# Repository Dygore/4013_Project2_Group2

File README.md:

# ECEN 4013 Project 2 Group 2

## About
This project is for Group 2's ECEN 4013 project 2, all of the code contained will be documented and cited if needed. The goal of this project is to create a circuit that can transmit IMU and GPS data through 3 means of communication (USB, UHF RF, and SD Card). This Github project will be used to store all of the code architecture, the details of the project are still being finalized and will be updated soon!

## Details
The current plan is to have two seperate circuits based on difficulty. The first circuit will be the main focus with the details contained below, the second circuit details have not been finalized yet.

Micro controller: Raspberry Pi Pico  
GPS: Adafruit Mini GPS PA1010D  
Radio: HC05  
IMU: Adafruit BNO055  
SD Card:  HW-125 SPI Micro SD Board  
Battery: LP103454  

## References
-https://microcontrollerslab.com/neo-6m-gps-module-raspberry-pi-pico-micropython/

Dylan Gore 10/24/2022

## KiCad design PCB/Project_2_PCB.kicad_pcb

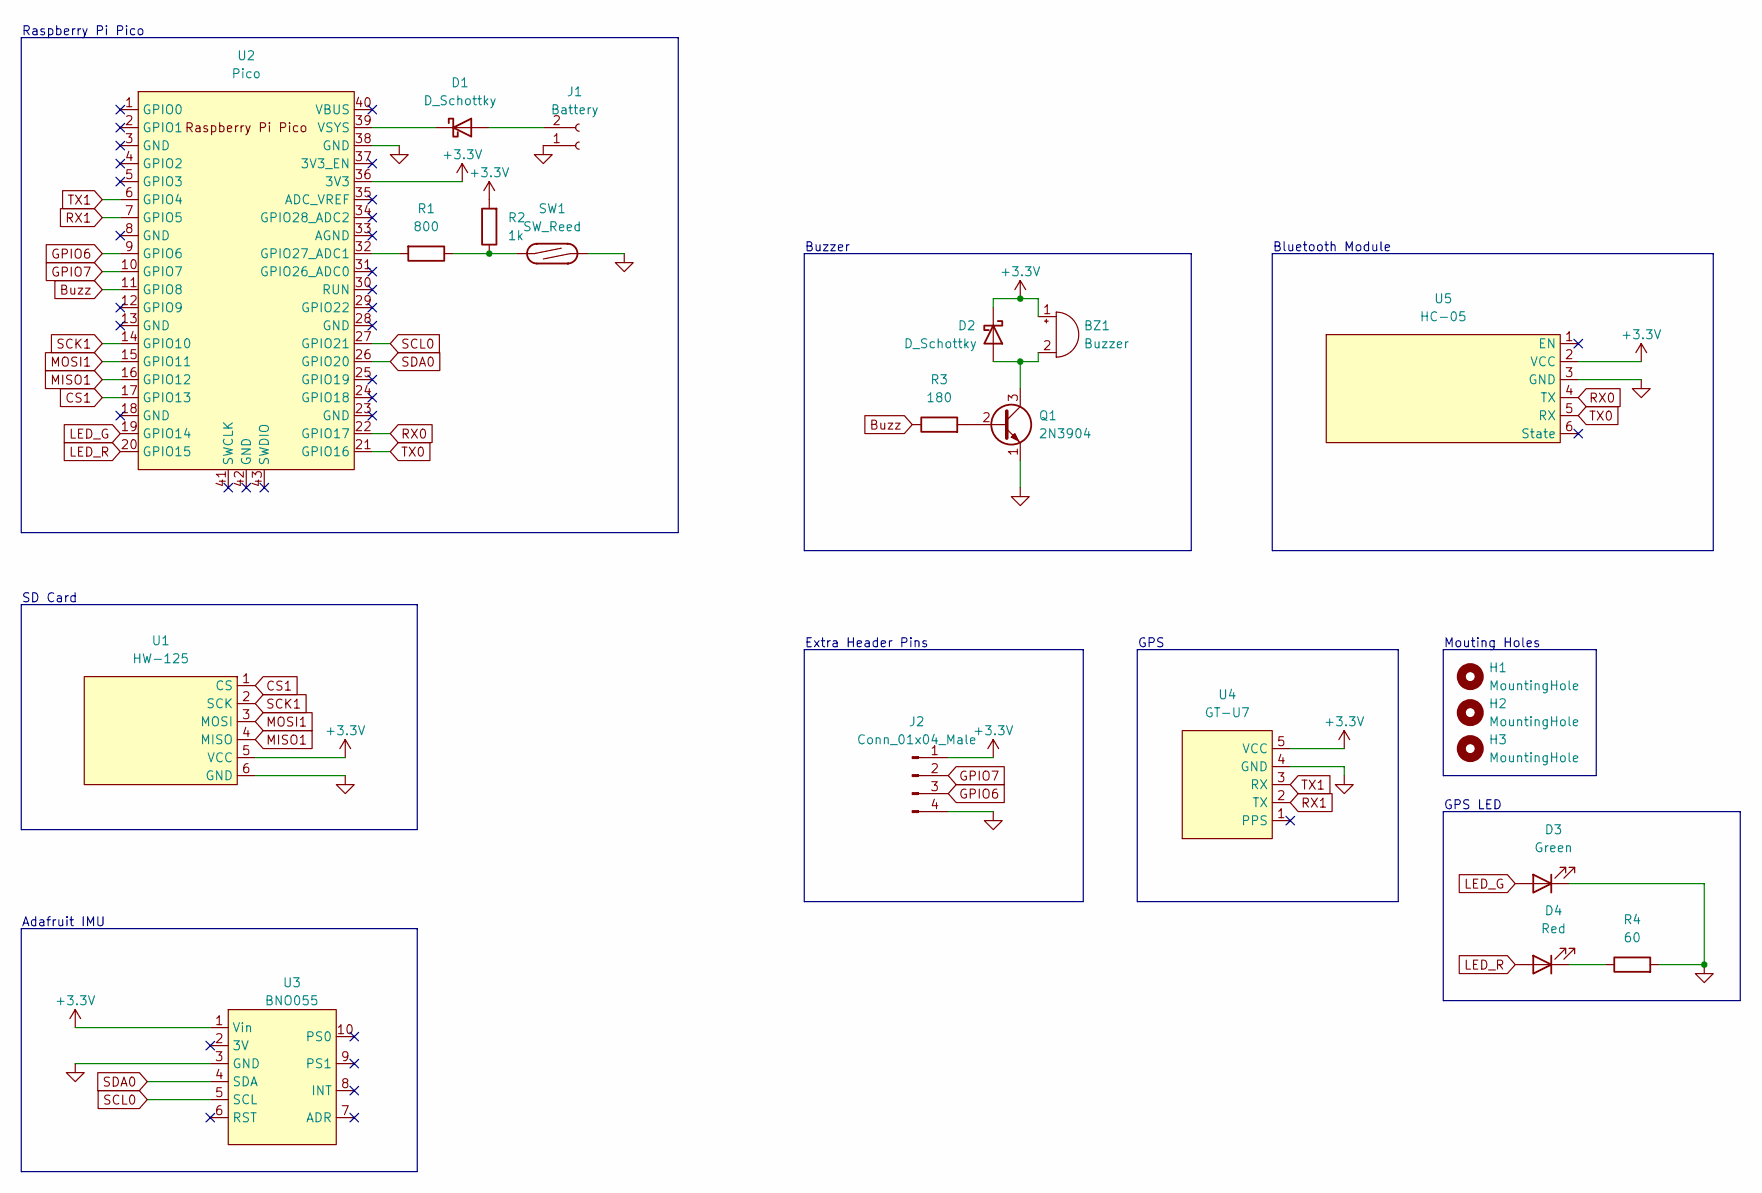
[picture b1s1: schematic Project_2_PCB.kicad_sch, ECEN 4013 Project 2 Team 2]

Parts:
BZ1: Buzzer; CMT8585397SMTTR
D1, D2: D_Schottky; D_1206_3216Metric
D3: Green; LED_D5.0mm
D4: Red; LED_D5.0mm
H1, H2, H3: MountingHole; MountingHole_4.3mm_M4_Pad_TopBottom
J1: Battery; JST_PH_S2B-PH-K_1x02_P2.00mm_Horizontal
J2: Conn_01x04_Male; PinHeader_1x04_P2.54mm_Vertical
Q1: 2N3904; SOT-23
R1: 800; R_Axial_DIN0207_L6.3mm_D2.5mm_P7.62mm_Horizontal
R2: 1k; R_Axial_DIN0207_L6.3mm_D2.5mm_P7.62mm_Horizontal
R3: 180; R_Axial_DIN0207_L6.3mm_D2.5mm_P7.62mm_Horizontal
R4: 60; R_Axial_DIN0207_L6.3mm_D2.5mm_P7.62mm_Horizontal
SW1: SW_Reed; R_Axial_DIN0207_L6.3mm_D2.5mm_P10.16mm_Horizontal
U1: HW-125
U2: Pico; RPi_Pico_SMD_TH
U3: BNO055
U4: GT-U7
U5: HC-05

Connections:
+3V3: BZ1.1 (-), D2.1 (K), J2.1, R2.2, U1.5 (VCC), U2.36 (3V3), U3.1 (Vin), U4.5 (VCC), U5.2 (VCC)
Buzz: R3.1, U2.11 (GPIO8)
CS1: U1.1 (CS), U2.17 (GPIO13)
GND: D3.1 (K), J1.1, J2.4, Q1.1 (E), R4.2, SW1.2, U1.6 (GND), U2.38 (GND), U3.3 (GND), U4.4 (GND), U5.3 (GND)
GPIO6: J2.3, U2.9 (GPIO6)
GPIO7: J2.2, U2.10 (GPIO7)
LED_G: D3.2 (A), U2.19 (GPIO14)
LED_R: D4.2 (A), U2.20 (GPIO15)
MISO1: U1.4 (MISO), U2.16 (GPIO12)
MOSI1: U1.3 (MOSI), U2.15 (GPIO11)
unnamed: BZ1.2 (+), D2.2 (A), Q1.3 (C)
unnamed: D1.1 (K), U2.39 (VSYS)
unnamed: D1.2 (A), J1.2
unnamed: D4.1 (K), R4.1
unnamed: Q1.2 (B), R3.2
unnamed: R1.1, R2.1, SW1.1
unnamed: R1.2, U2.32 (GPIO27_ADC1)
RX0: U2.22 (GPIO17), U5.4 (TX)
RX1: U2.7 (GPIO5), U4.2 (TX)
SCK1: U1.2 (SCK), U2.14 (GPIO10)
SCL0: U2.27 (GPIO21), U3.5 (SCL)
SDA0: U2.26 (GPIO20), U3.4 (SDA)
TX0: U2.21 (GPIO16), U5.5 (RX)
TX1: U2.6 (GPIO4), U4.3 (RX)

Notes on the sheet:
Extra Header Pins
Raspberry Pi Pico
Bluetooth Module
GPS
Adafruit IMU
Buzzer
GPS LED
Mouting Holes
SD Card

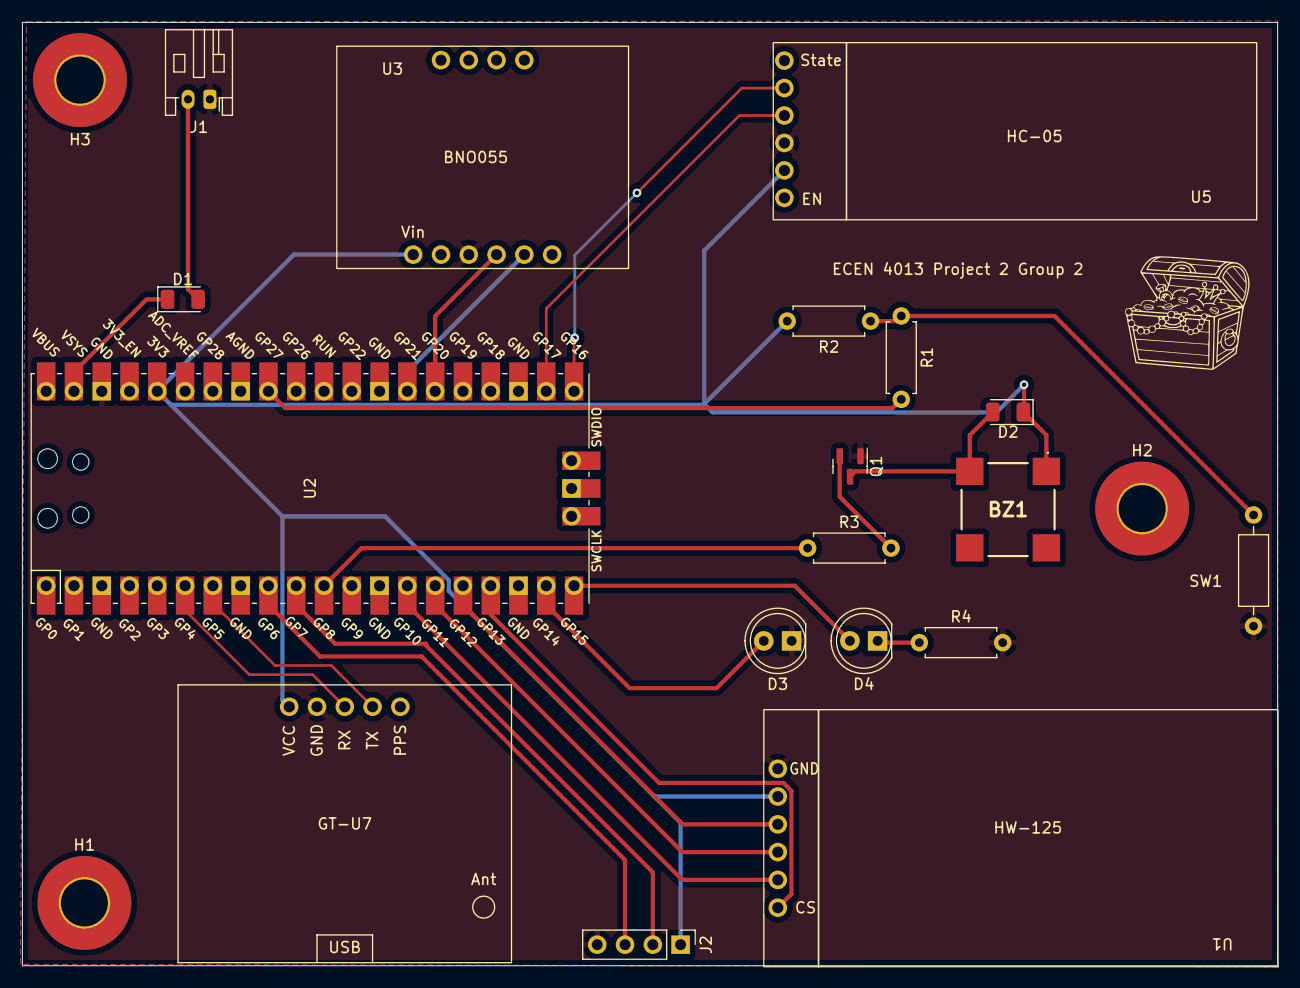
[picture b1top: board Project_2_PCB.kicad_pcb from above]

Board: 2 copper layers, 114.7 x 86.2 mm, 21 parts (0 on the bottom side), 24 nets.

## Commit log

2022-10-31 Added GPS Python File
2022-10-31 Updated References on ReadMe.md
2022-11-01 IMU w python and cpp
2022-11-02 Add PCB Files
2022-11-02 Update GPS File
2022-11-02 Create GPS Folder
2022-11-02 Move to GPS Folder
2022-11-02 Create PCB Folder
2022-11-02 Create IMU Folder
2022-11-02 Create SD Folder
2022-11-02 Create Bluetooth Folder
2022-11-02 Added PCB Files
2022-11-02 Rename IMU.cpp to IMU/IMU.cpp
2022-11-02 Rename IMU_py.py to IMU/IMU_py.py
2022-11-09 IMU Outputs
    using micropython, IMU_pico, bno055, and bno055_base work together to get the outputs of the IMU component
2022-11-13 Update Test
2022-11-14 Rename Test to Sd Card.py
2022-11-14 Create PiPythonCode
2022-11-14 Rename PiPythonCode to PiPythonCode.py
2022-11-14 Create PCPythonCode
2022-11-14 Create Bluetooth
2022-11-14 Create test
2022-11-14 Rename PCPythonCode to Bluetooth/PCPythonCode.py
2022-11-14 Rename PiPythonCode.py to Bluetooth/PiPythonCode.py
2022-11-14 Rename main.py to Main/main.py
